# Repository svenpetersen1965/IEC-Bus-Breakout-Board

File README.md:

# IEC-Bus-Breakout-Board
This is a breakout board for the Commodore C64/C128/C16/VIC-20 etc. IEC-Bus. The Purpose is connecting the IEC-Bus to a µController or miniComputer, like an Arduino, a Raspberry Pi (zero, pico, Pi1-4) etc.

It provides the required interface ICs and even 5V to 3.3V level shifters, which are required for e.g. the raspberry pis.

<b>This design is not yet tested, and this is a preliminary release.</b>

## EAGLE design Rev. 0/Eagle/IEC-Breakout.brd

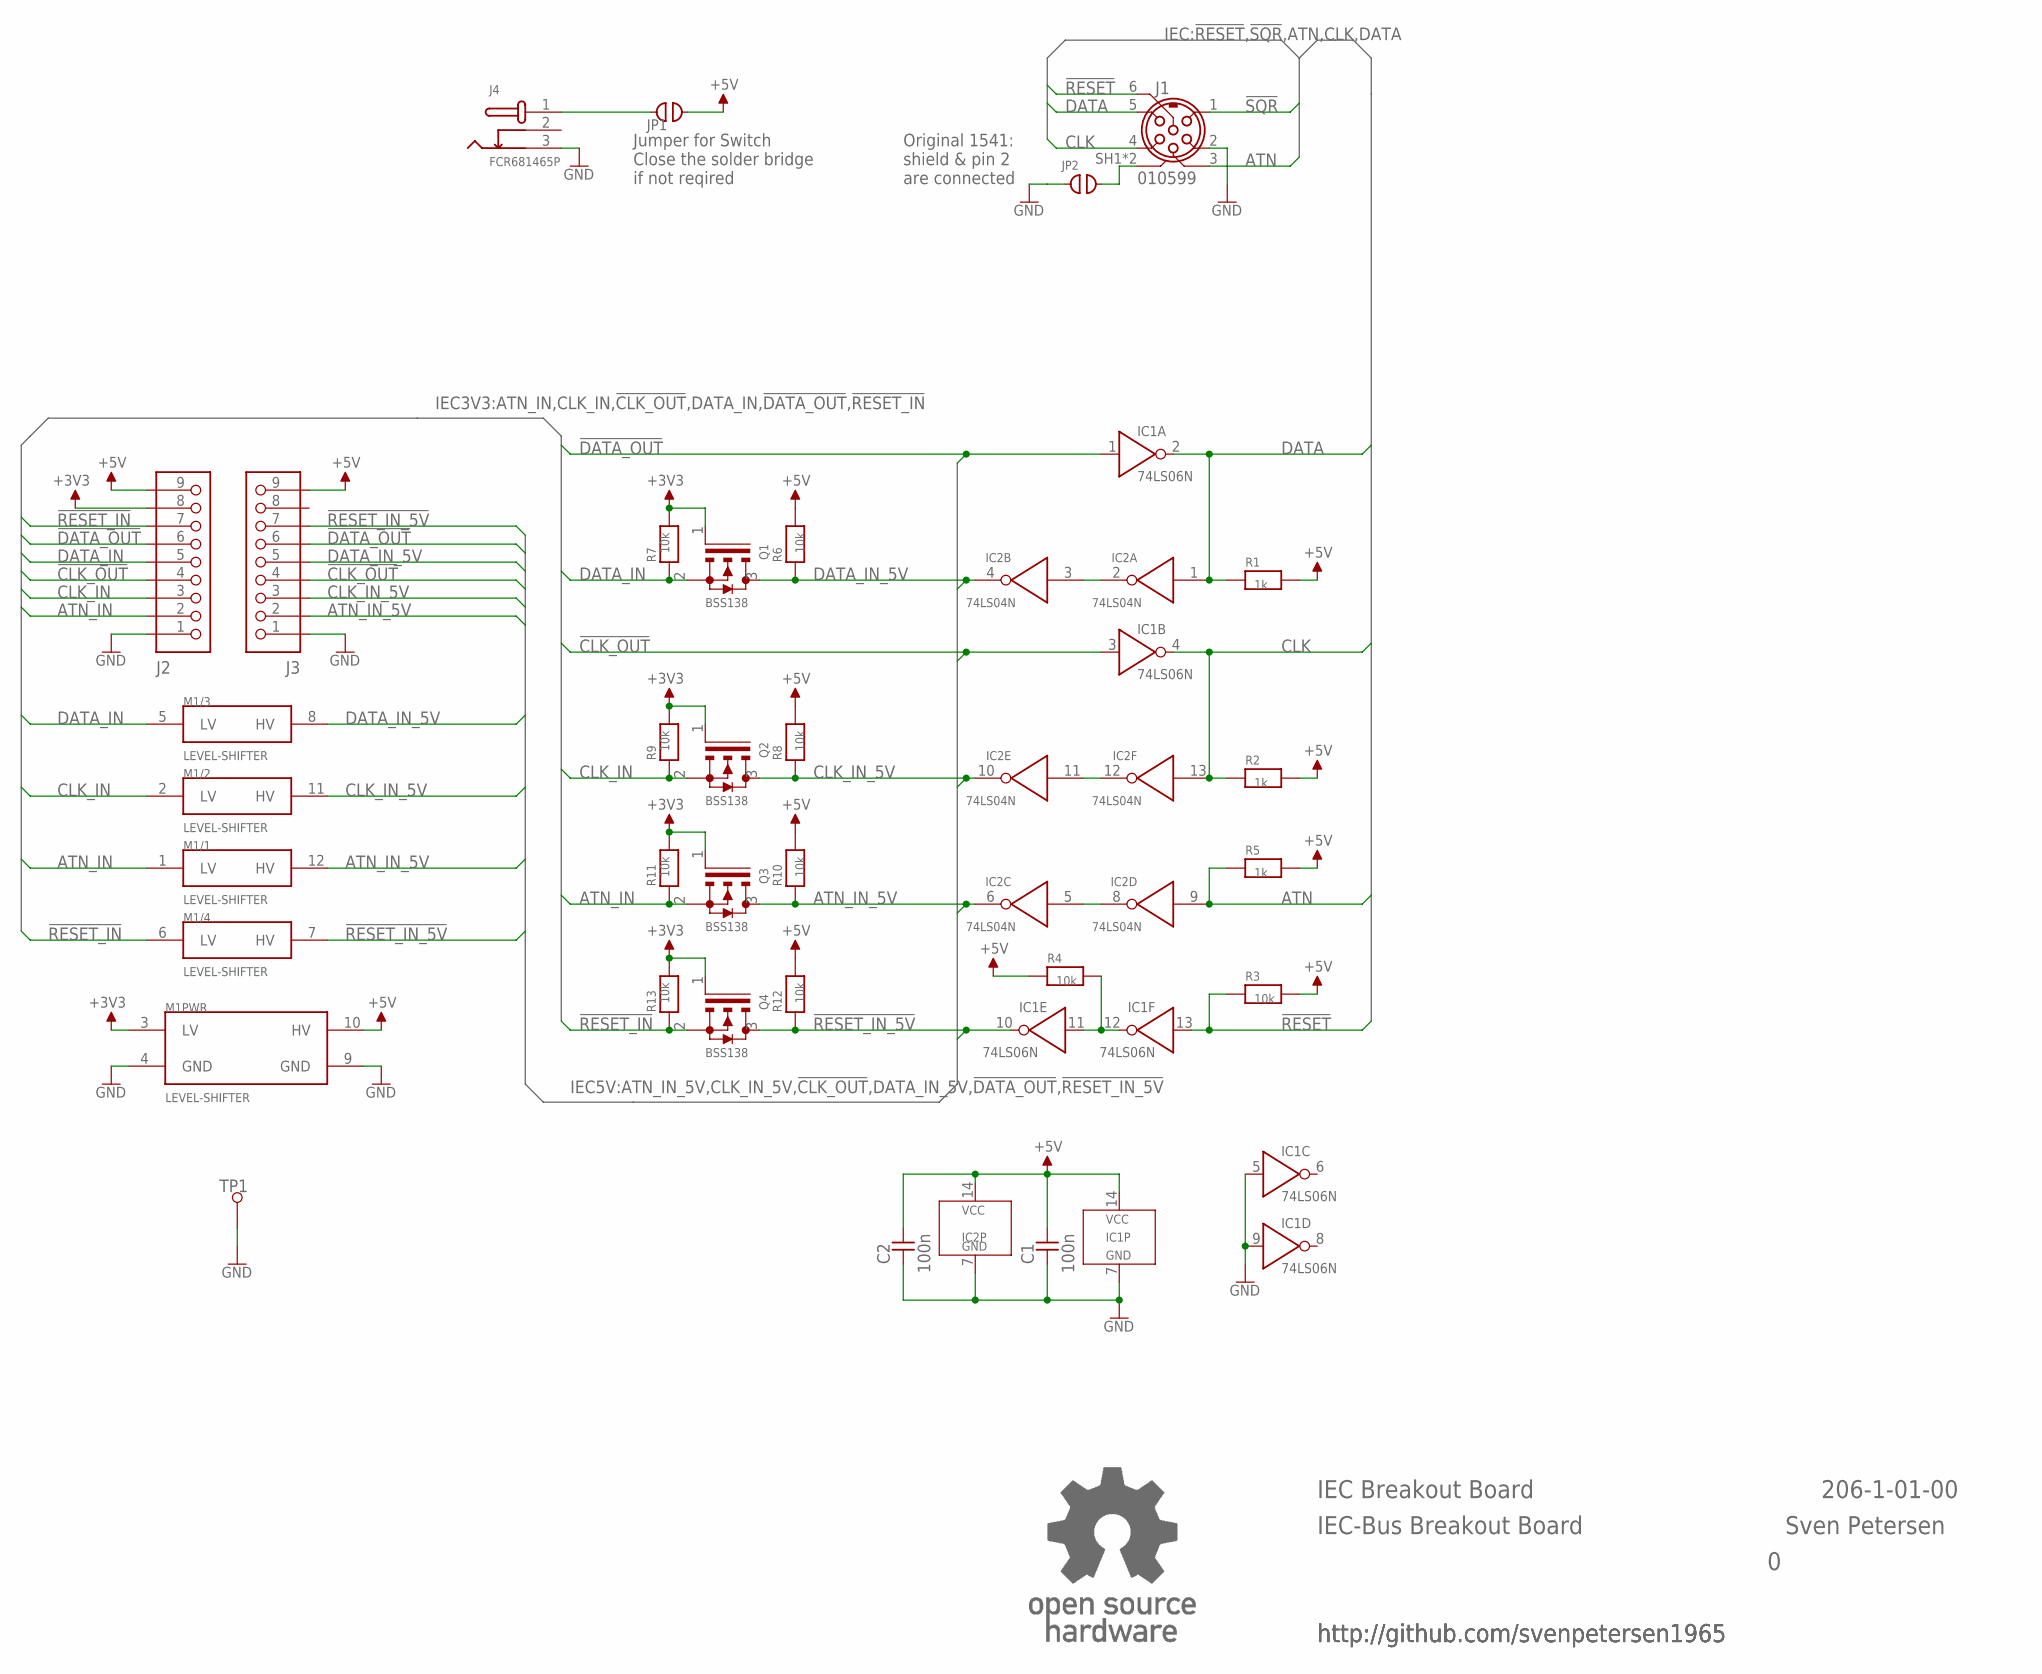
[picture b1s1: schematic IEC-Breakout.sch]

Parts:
C1, C2: 100n; C-2,5
IC1: 74LS06N; DIL-14
IC2: 74LS04N; DIL-14
J1: 010599
J2, J3: PINHD-1X9; 1X09
J4: FCR681465P
JP1: COMBI_2P; COMBI-2P
JP2: OPEN; CP_OP
M1: LEVEL-SHIFTER; L-SHIFTER
Q1, Q2, Q3, Q4: BSS138; SOT23
R1, R2, R5: 1k; R-10
R3, R4: 10k; R-10
R6, R7, R8, R9, R10, R11, R12, R13: 10k; 0805
TP1: L1,2_R; 1,2MM_R
U$31: OPEN_SOURCE_HW; OPENHW

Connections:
!CLK_OUT: IC1.3 (I), J2.4, J3.4
!DATA_OUT: IC1.1 (I), J2.6, J3.6
!RESET: IC1.13 (I), J1.6, R3.1
!RESET_IN: J2.7, M1.6 (LV), Q4.2 (S), R13.1
!RESET_IN_5V: IC1.10 (O), J3.7, M1.7 (HV), Q4.3 (D), R12.1
!SQR: J1.1
+3V3: J2.8, M1.3 (LV), Q1.1 (G), Q2.1 (G), Q3.1 (G), Q4.1 (G), R7.2, R9.2, R11.2, R13.2
+5V: C1.2, C2.2, IC1.14 (VCC), IC2.14 (VCC), J2.9, J3.9, JP1.2, M1.10 (HV), R1.2, R2.2, R3.2, R4.1, R5.2, R6.2, R8.2, R10.2, R12.2
ATN: IC2.9 (I), J1.3, R5.1
ATN_IN: J2.2, M1.1 (LV), Q3.2 (S), R11.1
ATN_IN_5V: IC2.6 (O), J3.2, M1.12 (HV), Q3.3 (D), R10.1
CLK: IC1.4 (O), IC2.13 (I), J1.4, R2.1
CLK_IN: J2.3, M1.2 (LV), Q2.2 (S), R9.1
CLK_IN_5V: IC2.10 (O), J3.3, M1.11 (HV), Q2.3 (D), R8.1
DATA: IC1.2 (O), IC2.1 (I), J1.5, R1.1
DATA_IN: J2.5, M1.5 (LV), Q1.2 (S), R7.1
DATA_IN_5V: IC2.4 (O), J3.5, M1.8 (HV), Q1.3 (D), R6.1
GND: C1.1, C2.1, IC1.5 (I), IC1.7 (GND), IC1.9 (I), IC2.7 (GND), J1.2, J2.1, J3.1, J4.3, JP2.1, M1.4 (GND), M1.9 (GND), TP1.1
unnamed: J1.SH1 (SH), J1.SH2 (SH), JP2.2
unnamed: IC2.2 (O), IC2.3 (I)
unnamed: J4.1, JP1.1
unnamed: IC2.11 (I), IC2.12 (O)
unnamed: IC2.5 (I), IC2.8 (O)
unnamed: IC1.11 (I), IC1.12 (O), R4.2

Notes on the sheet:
Original 1541: shield & pin 2 are connected
Jumper for Switch Close the solder bridge if not reqired
IEC Breakout Board
IEC-Bus Breakout Board
Sven Petersen
206-1-01-00
http://github.com/svenpetersen1965

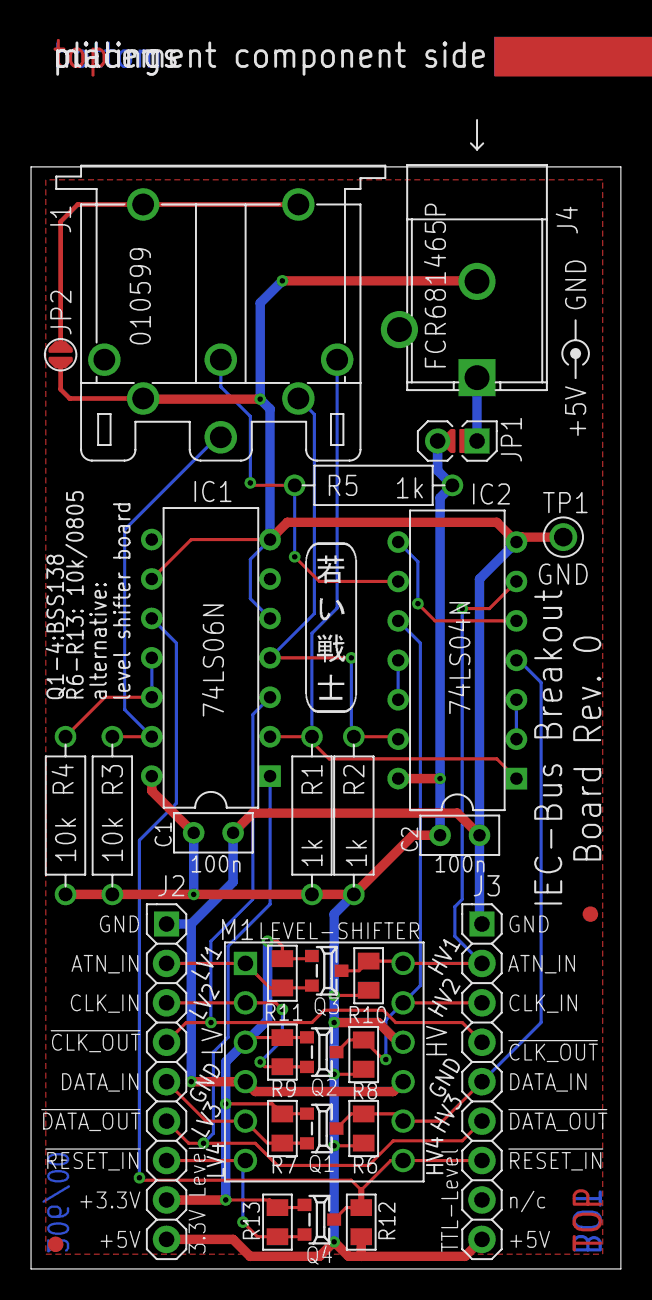
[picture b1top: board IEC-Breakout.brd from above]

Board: 2 copper layers, 38.0 x 79.8 mm, 35 parts (1 on the bottom side), 23 nets.

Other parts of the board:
U$32: 2LAYER
U$33, U$34: SMD_REF_R1MM
U$35: PCB-TITLE/
U$36: SVEN_TAG

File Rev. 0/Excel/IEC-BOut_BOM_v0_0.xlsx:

IEC-Bus Breakout Board Rev. 0
Bill of Material Rev. 0.0
Pos. | Qty | Value | Footprint | Ref.-No. | Comment
1 | 1 | 206-2-01-00 | 2 Layer | PCB Rev. 0 | 2 layer, Cu 35µ, HASL, 71.0mm x 38.0mm, 1.6mm FR4
 | 2 | 1x9 pin header, 2.54mm | 1X09 | J2, J3 | standard pin header
 | 1 | 010599 | 10599 | J1 | Lumberg, e.g. Reichelt 010599 06, tme.eu: 0105-06
 | 2 | 100n | C-2,5 | C1, C2 | 100n/50V ceramic capacitor, 2.54mm pitch
 | 8 | 10k | 0805 | R6, R7, R8, R9, R10, R11, R12, R13 | SMD 0805, 5% or better, for on-board level shifter
 | 2 | 10k | R-10 | R3, R4 | THT resistor, 0.5W, 5%
 | 3 | 1k | R-10 | R1, R2, R5 | THT resistor, 0.5W, 5%
 | 1 | 74LS04N | DIL-14 | IC2 | Logic IC (TTL)
 | 1 | 74LS06N | DIL-14 | IC1 | Logic IC (TTL)
 | 4 | BSS138 | SOT23 | Q1, Q2, Q3, Q4 | MOSFET, for on-board level shifter
 | 1 | COMBI_2P | COMBI-2P | JP1 | for power switch, or solderbridge for always on
 | 1 | FCR681465P | FCR681465P | J4 | Cliff, Reichelt: CLIFF FCR681465P, tme.eu: FCR681465P
 | 1 | L1,2_R | 1,2MM_R | TP1 | dnp, GND pin for debugging purposes
 | 1 | LEVEL-SHIFTER | L-SHIFTER | M1 | Level shifter module, in case, the onboard level shifter circuit is not placed
